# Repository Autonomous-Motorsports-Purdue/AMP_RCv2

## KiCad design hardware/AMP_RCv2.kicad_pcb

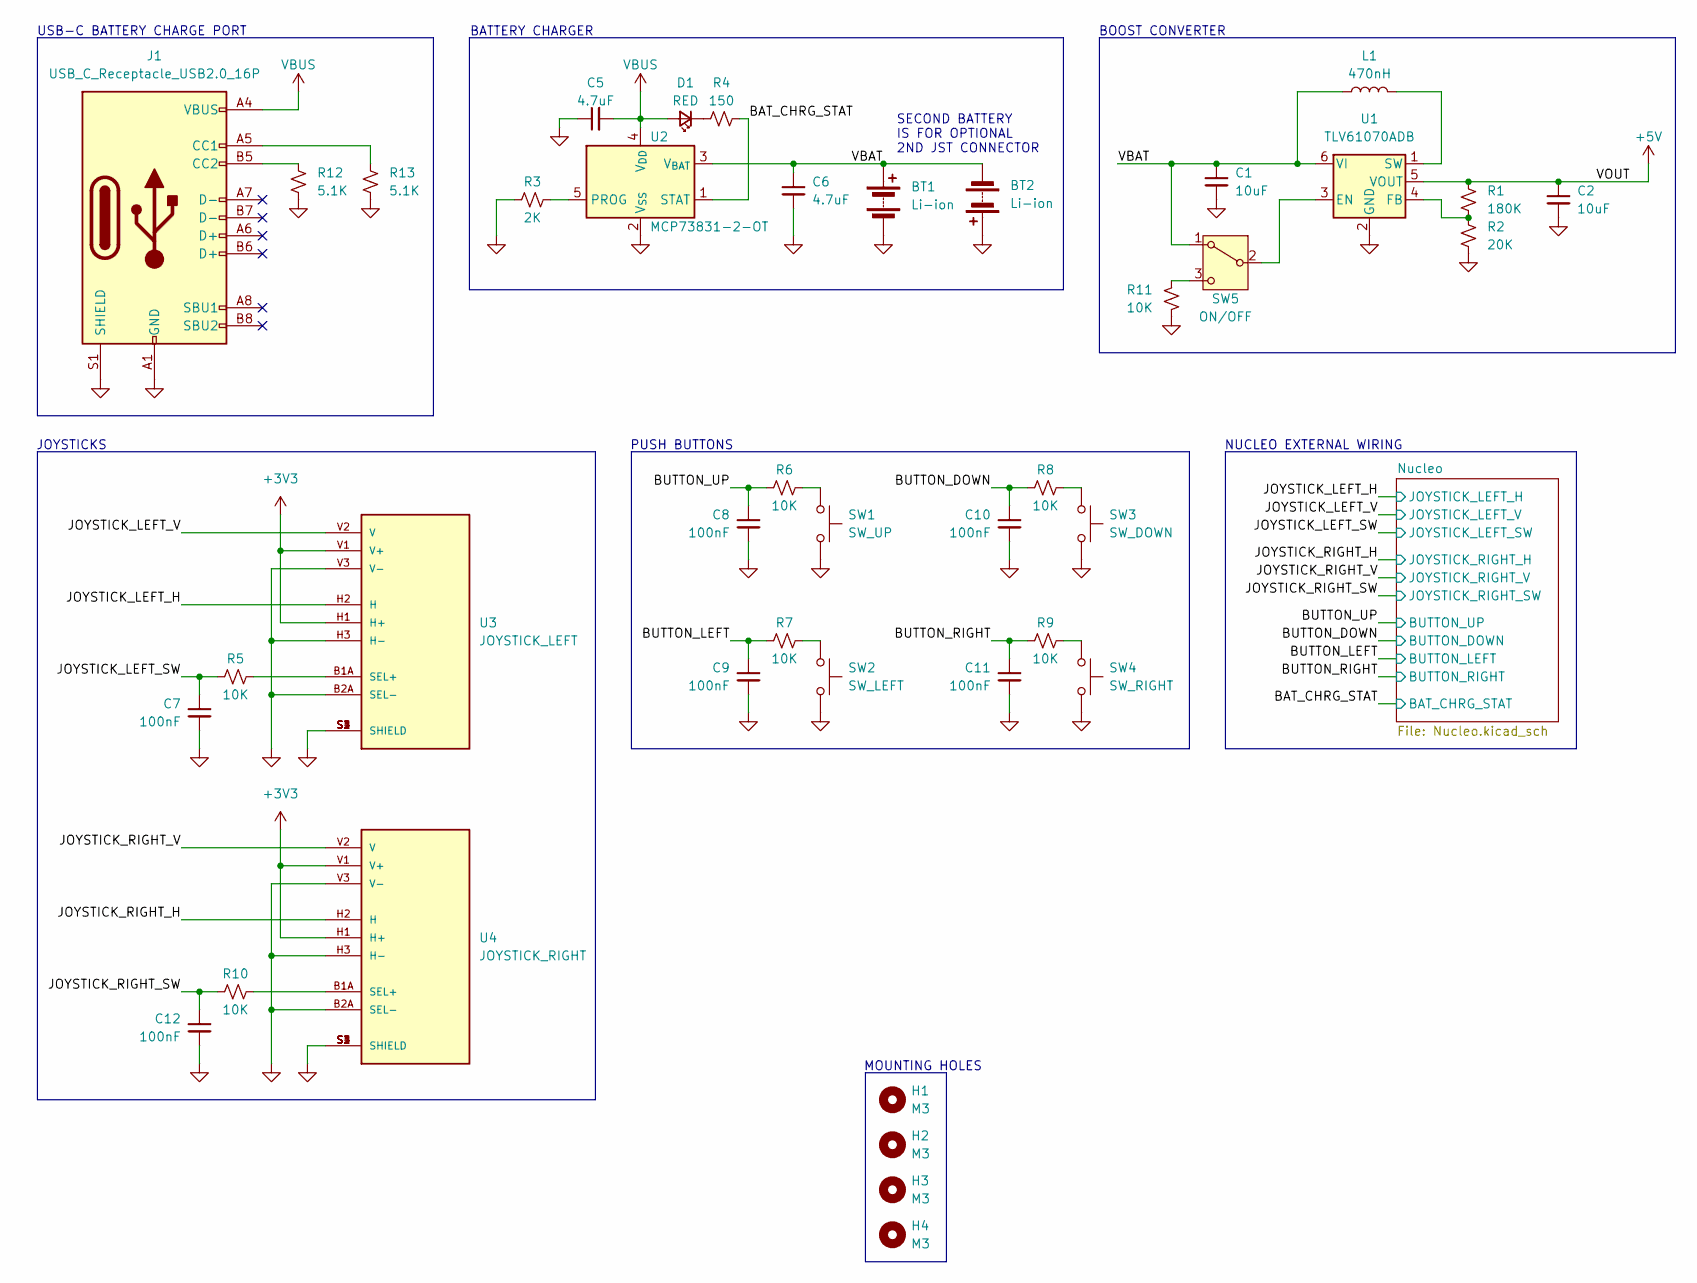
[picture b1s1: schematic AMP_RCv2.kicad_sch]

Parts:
BT1, BT2: Li-ion; JST_PH_B2B-PH-K_1x02_P2.00mm_Vertical
C1, C2: 10uF; C_0805_2012Metric_Pad1.18x1.45mm_HandSolder
C5, C6: 4.7uF; C_0805_2012Metric_Pad1.18x1.45mm_HandSolder
C7, C8, C9, C10, C11, C12: 100nF; C_0805_2012Metric_Pad1.18x1.45mm_HandSolder
D1: RED; LED_0805_2012Metric_Pad1.15x1.40mm_HandSolder
H1, H2, H3, H4: M3; MountingHole_3.2mm_M3
J1: USB_C_Receptacle_USB2.0_16P; USB_C_Receptacle_GCT_USB4085
L1: 470nH; L_Wuerth_MAPI-4030
R1: 180K; R_0805_2012Metric_Pad1.20x1.40mm_HandSolder
R2: 20K; R_0805_2012Metric_Pad1.20x1.40mm_HandSolder
R3: 2K; R_0805_2012Metric_Pad1.20x1.40mm_HandSolder
R4: 150; R_0805_2012Metric_Pad1.20x1.40mm_HandSolder
R5, R6, R7, R8, R9, R10, R11: 10K; R_0805_2012Metric_Pad1.20x1.40mm_HandSolder
R12, R13: 5.1K; R_0805_2012Metric_Pad1.20x1.40mm_HandSolder
SW1: SW_UP; SW_PUSH-12mm
SW2: SW_LEFT; SW_PUSH-12mm
SW3: SW_DOWN; SW_PUSH-12mm
SW4: SW_RIGHT; SW_PUSH-12mm
SW5: ON/OFF; SLW-121586-5A-D
U1: TLV61070ADB; SOT-23-6
U2: MCP73831-2-OT; SOT-23-5
U3: JOYSTICK_LEFT; XDCR_COM-09032; PARTREV N/A
U4: JOYSTICK_RIGHT; XDCR_COM-09032; PARTREV N/A

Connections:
+3V3: U3.H1 (H+), U3.V1 (V+), U4.H1 (H+), U4.V1 (V+); also elsewhere on the board
+5V: C2.1, R1.1, U1.5 (VOUT); also elsewhere on the board
/BAT_CHRG_STAT: R4.2, U2.1 (STAT); also elsewhere on the board
/BUTTON_DOWN: C10.1, R8.1; also elsewhere on the board
/BUTTON_LEFT: C9.1, R7.1; also elsewhere on the board
/BUTTON_RIGHT: C11.1, R9.1; also elsewhere on the board
/BUTTON_UP: C8.1, R6.1; also elsewhere on the board
/JOYSTICK_LEFT_H: U3.H2 (H); also elsewhere on the board
/JOYSTICK_LEFT_SW: C7.1, R5.1; also elsewhere on the board
/JOYSTICK_LEFT_V: U3.V2 (V); also elsewhere on the board
/JOYSTICK_RIGHT_H: U4.H2 (H); also elsewhere on the board
/JOYSTICK_RIGHT_SW: C12.1, R10.1; also elsewhere on the board
/JOYSTICK_RIGHT_V: U4.V2 (V); also elsewhere on the board
/VBAT: BT1.1 (+), BT2.2 (-), C1.1, C6.1, L1.1, SW5.1 (A), U1.6 (VI), U2.3 (V_{BAT})
GND: BT1.2 (-), BT2.1 (+), C1.2, C2.2, C5.1, C6.2, C7.2, C8.2, C9.2, C10.2, C11.2, C12.2, J1.A1 (GND), J1.A12 (GND), J1.B1 (GND), J1.B12 (GND), J1.S1 (SHIELD), R2.2, R3.1, R11.2, R12.2, R13.2, SW1.2, SW2.2, SW3.2, SW4.2, U1.2 (GND), U2.2 (V_{SS}), U3.B2A (SEL-), U3.H3 (H-), U3.S1 (SHIELD), U3.S2 (SHIELD), U3.S3 (SHIELD), U3.S4 (SHIELD), U3.V3 (V-), U4.B2A (SEL-), U4.H3 (H-), U4.S1 (SHIELD), U4.S2 (SHIELD), U4.S3 (SHIELD), U4.S4 (SHIELD), U4.V3 (V-); also elsewhere on the board
unnamed: D1.1 (K), R4.1
unnamed: J1.A5 (CC1), R13.1
unnamed: J1.B5 (CC2), R12.1
unnamed: R6.2, SW1.1
unnamed: R7.2, SW2.1
unnamed: R8.2, SW3.1
unnamed: R9.2, SW4.1
unnamed: SW5.2 (B), U1.3 (EN)
unnamed: R11.1, SW5.3 (C)
unnamed: R1.2, R2.1, U1.4 (FB)
unnamed: L1.2, U1.1 (SW)
unnamed: R3.2, U2.5 (PROG)
unnamed: R5.2, U3.B1A (SEL+)
unnamed: R10.2, U4.B1A (SEL+)
VBUS: C5.2, D1.2 (A), J1.A4 (VBUS), J1.A9 (VBUS), J1.B4 (VBUS), J1.B9 (VBUS), U2.4 (V_{DD})

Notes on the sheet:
JOYSTICKS
BATTERY CHARGER
MOUNTING HOLES
BOOST CONVERTER
USB-C BATTERY CHARGE PORT
NUCLEO EXTERNAL WIRING
PUSH BUTTONS
SECOND BATTERY IS FOR OPTIONAL 2ND JST CONNECTOR

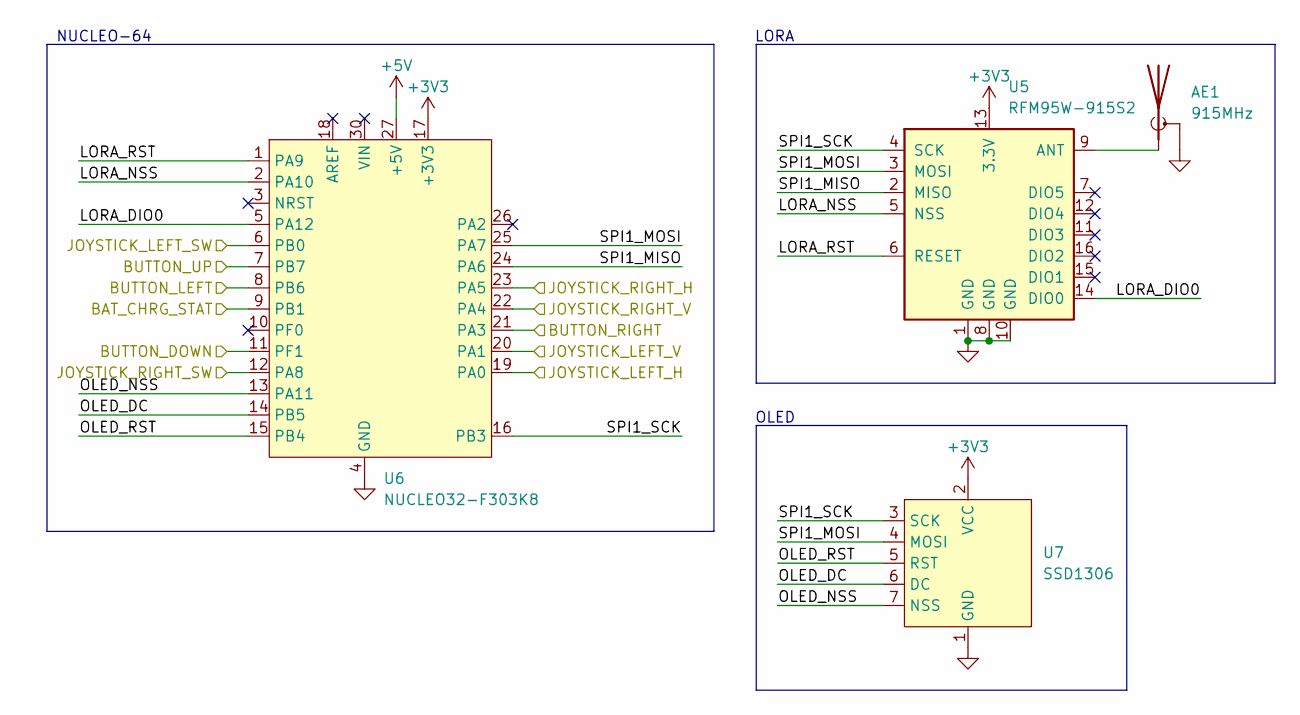
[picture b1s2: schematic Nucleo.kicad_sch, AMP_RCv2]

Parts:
AE1: 915MHz; SMA_Amphenol_132291_Vertical
U5: RFM95W-915S2; HOPERF_RFM9XW_SMD
U6: NUCLEO32-F303K8; NUCLEO32
U7: SSD1306; SSD1306_SPI

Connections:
+3V3: U5.13 (3.3V), U6.17 (+3V3), U7.2 (VCC); also elsewhere on the board
+5V: U6.27 (+5V); also elsewhere on the board
/BAT_CHRG_STAT: U6.9 (PB1); also elsewhere on the board
/BUTTON_DOWN: U6.11 (PF1); also elsewhere on the board
/BUTTON_LEFT: U6.8 (PB6); also elsewhere on the board
/BUTTON_RIGHT: U6.21 (PA3); also elsewhere on the board
/BUTTON_UP: U6.7 (PB7); also elsewhere on the board
/JOYSTICK_LEFT_H: U6.19 (PA0); also elsewhere on the board
/JOYSTICK_LEFT_SW: U6.6 (PB0); also elsewhere on the board
/JOYSTICK_LEFT_V: U6.20 (PA1); also elsewhere on the board
/JOYSTICK_RIGHT_H: U6.23 (PA5); also elsewhere on the board
/JOYSTICK_RIGHT_SW: U6.12 (PA8); also elsewhere on the board
/JOYSTICK_RIGHT_V: U6.22 (PA4); also elsewhere on the board
/Nucleo/LORA_DIO0: U5.14 (DIO0), U6.5 (PA12)
/Nucleo/LORA_NSS: U5.5 (NSS), U6.2 (PA10)
/Nucleo/LORA_RST: U5.6 (RESET), U6.1 (PA9)
/Nucleo/OLED_DC: U6.14 (PB5), U7.6 (DC)
/Nucleo/OLED_NSS: U6.13 (PA11), U7.7 (NSS)
/Nucleo/OLED_RST: U6.15 (PB4), U7.5 (RST)
/Nucleo/SPI1_MISO: U5.2 (MISO), U6.24 (PA6)
/Nucleo/SPI1_MOSI: U5.3 (MOSI), U6.25 (PA7), U7.4 (MOSI)
/Nucleo/SPI1_SCK: U5.4 (SCK), U6.16 (PB3), U7.3 (SCK)
GND: AE1.2 (Shield), U5.1 (GND), U5.8 (GND), U5.10 (GND), U6.4 (GND), U6.29 (GND), U7.1 (GND); also elsewhere on the board
unnamed: AE1.1 (A), U5.9 (ANT)

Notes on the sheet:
NUCLEO-64
OLED
LORA

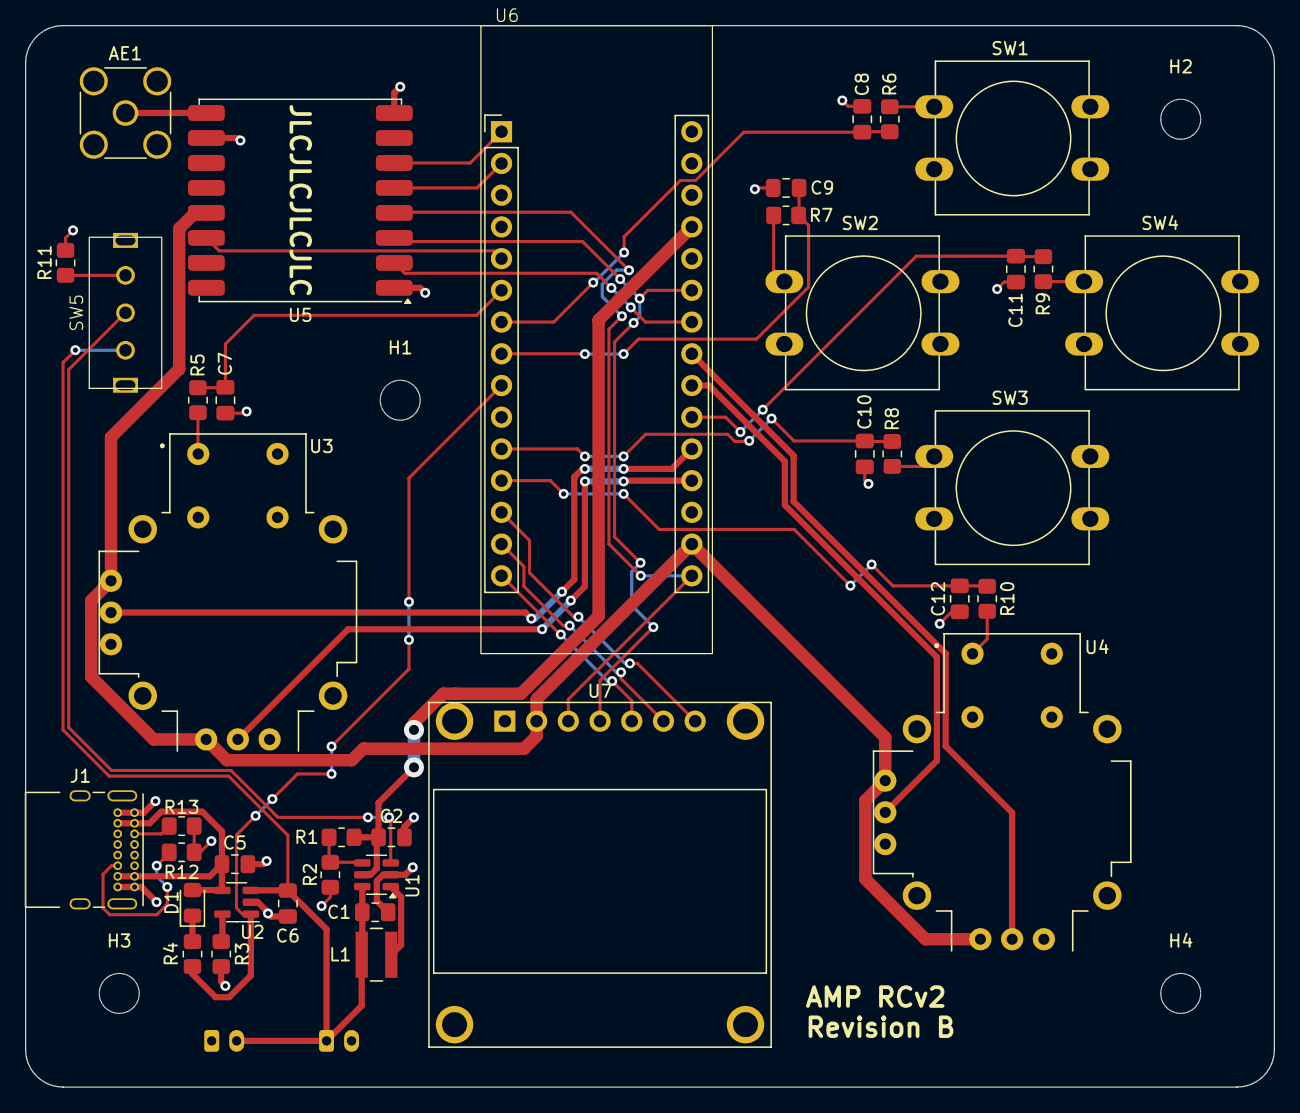
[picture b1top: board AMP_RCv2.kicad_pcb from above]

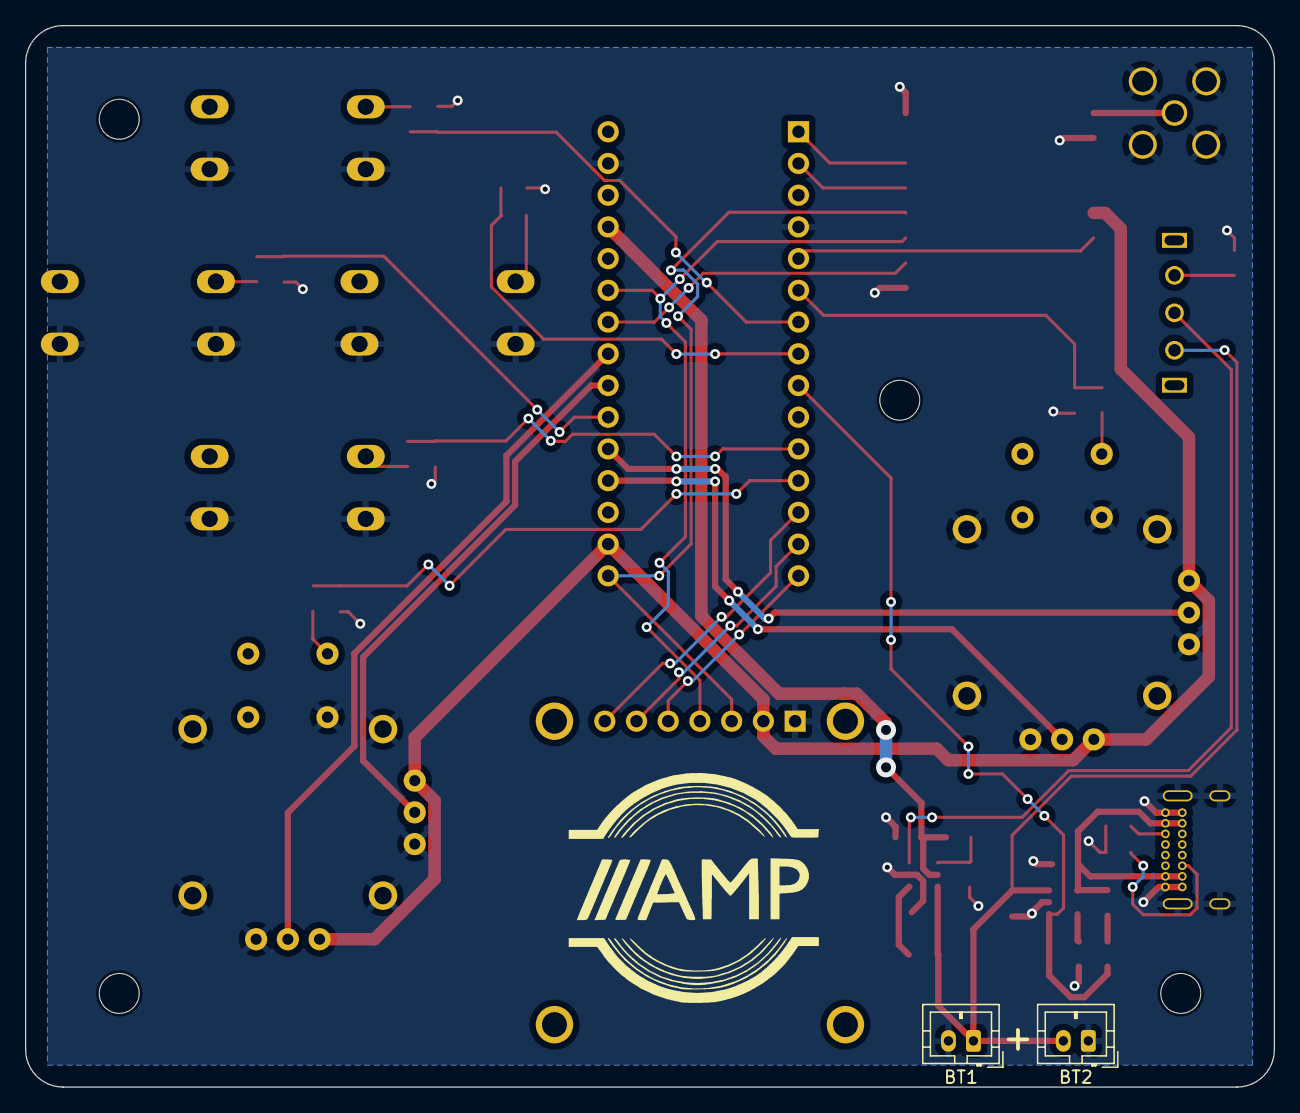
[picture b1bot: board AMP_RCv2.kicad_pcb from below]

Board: 2 copper layers, 100.0 x 85.0 mm, 45 parts (2 on the bottom side), 40 nets.

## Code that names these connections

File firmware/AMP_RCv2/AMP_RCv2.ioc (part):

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Mcu.Name=STM32F303K(6-8)Tx
Mcu.Package=LQFP32
Mcu.UserName=STM32F303K8Tx
PA0.GPIOParameters=GPIO_Label
PA0.GPIO_Label=JOYSTICK_LEFT_H
PA0.Mode=IN1-Single-Ended
PA0.Signal=ADC1_IN1
PA1.GPIOParameters=GPIO_Label
PA1.GPIO_Label=JOYSTICK_LEFT_V
PA1.Mode=IN2-Single-Ended
PA1.Signal=ADC1_IN2
PA10.GPIOParameters=GPIO_Label
PA10.GPIO_Label=LORA_NSS
PA10.Signal=GPIO_Output
PA11.GPIOParameters=GPIO_Label
PA11.GPIO_Label=OLED_NSS
PA11.Signal=GPIO_Output
PA12.GPIOParameters=GPIO_Label
PA12.GPIO_Label=LORA_DIO0
PA12.Signal=GPXTI12
PA13.GPIOParameters=GPIO_Label
PA13.GPIO_Label=SWDIO
PA13.Mode=Serial_Wire
PA13.Signal=SYS_JTMS-SWDIO
PA14.GPIOParameters=GPIO_Label
PA14.GPIO_Label=SWCLK
PA14.Mode=Serial_Wire
PA14.Signal=SYS_JTCK-SWCLK
PA15.GPIOParameters=GPIO_Label
PA15.GPIO_Label=VCP_RX
PA15.Mode=Asynchronous
PA15.Signal=USART2_RX
PA2.GPIOParameters=GPIO_Label
PA2.GPIO_Label=VCP_TX
PA2.Mode=Asynchronous
PA2.Signal=USART2_TX
PA3.GPIOParameters=GPIO_PuPd,GPIO_Label,GPIO_ModeDefaultEXTI
PA3.GPIO_Label=BTN_RIGHT
PA3.GPIO_ModeDefaultEXTI=GPIO_MODE_IT_FALLING
PA3.GPIO_PuPd=GPIO_PULLUP
PA3.Signal=GPXTI3
PA4.GPIOParameters=GPIO_Label
PA4.GPIO_Label=JOYSTICK_RIGHT_V
PA4.Mode=IN1-Single-Ended
PA4.Signal=ADC2_IN1
PA5.GPIOParameters=GPIO_Label
PA5.GPIO_Label=JOYSTICK_RIGHT_H
PA5.Mode=IN2-Single-Ended
PA5.Signal=ADC2_IN2
PA6.Mode=Full_Duplex_Master
PA6.Signal=SPI1_MISO
PA7.Mode=Full_Duplex_Master
PA7.Signal=SPI1_MOSI
PA8.GPIOParameters=GPIO_Label
PA8.GPIO_Label=JOYSTICK_R_SW
PA8.Signal=GPXTI8
PA9.GPIOParameters=GPIO_Label
PA9.GPIO_Label=LORA_RST
PA9.Signal=GPIO_Output
PB0.GPIOParameters=GPIO_Label,GPIO_ModeDefaultEXTI
PB0.GPIO_Label=JOYSTICK_L_SW
PB0.GPIO_ModeDefaultEXTI=GPIO_MODE_IT_RISING
PB0.Signal=GPXTI0
PB1.GPIOParameters=GPIO_Label
PB1.GPIO_Label=BAT_CHRG_STAT
PB1.Signal=GPIO_Input
PB3.Mode=Full_Duplex_Master
PB3.Signal=SPI1_SCK
PB4.GPIOParameters=GPIO_Label
PB4.GPIO_Label=OLED_RST
PB4.Signal=GPIO_Output
PB5.GPIOParameters=GPIO_Label
PB5.GPIO_Label=OLED_DC
PB5.Signal=GPIO_Output
PB6.GPIOParameters=GPIO_PuPd,GPIO_Label,GPIO_ModeDefaultEXTI
PB6.GPIO_Label=BTN_LEFT
PB6.GPIO_ModeDefaultEXTI=GPIO_MODE_IT_FALLING
PB6.GPIO_PuPd=GPIO_PULLUP
PB6.Signal=GPXTI6
PB7.GPIOParameters=GPIO_PuPd,GPIO_Label,GPIO_ModeDefaultEXTI
PB7.GPIO_Label=BTN_UP
PB7.GPIO_ModeDefaultEXTI=GPIO_MODE_IT_FALLING
PB7.GPIO_PuPd=GPIO_PULLUP
PB7.Signal=GPXTI7
PF0\ /\ OSC_IN.GPIOParameters=GPIO_Label
PF0\ /\ OSC_IN.GPIO_Label=MCO
PF0\ /\ OSC_IN.Mode=HSE-External-Clock-Source
PF0\ /\ OSC_IN.Signal=RCC_OSC_IN
PF1\ /\ OSC_OUT.GPIOParameters=GPIO_PuPd,GPIO_Label,GPIO_ModeDefaultEXTI
PF1\ /\ OSC_OUT.GPIO_Label=BTN_DOWN
PF1\ /\ OSC_OUT.GPIO_ModeDefaultEXTI=GPIO_MODE_IT_FALLING
PF1\ /\ OSC_OUT.GPIO_PuPd=GPIO_PULLUP
PF1\ /\ OSC_OUT.Signal=GPXTI1
RCC.HSEPLLFreq_Value=8000000
RCC.HSE_VALUE=8000000
RCC.SYSCLKFreq_VALUE=64000000
RCC.SYSCLKSourceVirtual=RCC_SYSCLKSOURCE_PLLCLK
board=NUCLEO-F303K8
boardIOC=true

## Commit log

2024-03-14 WebBench
2024-03-14 IOC mappings
2024-03-14 Schematic and placing of most parts
2024-03-15 Change IOC for better routing
2024-03-15 IOC remapping for better routing
2024-03-15 Finish routing
2024-03-15 Add Nucleo-32 docs
2024-03-15 KiCAD 8.0 migration
2024-03-27 Ignore KiCAD lck files
2024-03-27 Fix incorrect power switch wiring
2024-03-27 Replace USB-C port
2024-03-27 Increase ground plane size
2024-03-28 Replace boost converter
2024-03-28 Clean up schematic and add optional second battery connector
2024-03-28 Remove old WEBENCH design
2024-03-28 Update 3D models
2024-04-04 Finishing touches
2024-04-04 Change text size
2024-04-30 I prey to the lord this uploads
2024-05-02 Remove extra Eclipse files
2024-05-02 Ignore CubeIDE files
2024-05-02 Remove files
2024-05-02 Update gitignore
2024-05-02 Update ioc peripheral generation format
2024-05-02 Clean up state machine
2024-05-02 Revert "Remove extra Eclipse files"
    This reverts commit c2f57aa422bf200500a915565af12b525244114b.
2024-05-02 Remove unused constants
2024-09-27 Started on screen - needs hw testing
2024-10-31 screen actually works now with hello world :)
2024-10-31 created basic state screens
2024-11-01 added startup image
2025-02-02 testing code from last semester. to be removed
2025-02-02 forgot to add file
2025-03-30 init lora
2025-09-28 start of conversion
2025-09-28 removed upload port from platformio.ini
2025-10-20 Add files via upload
    Updated app_statemachine code with improved OLED display
2025-10-20 Add files via upload
    Updates supporting files for the OLED display
2025-10-26 Configured throttle and steering
2025-10-27 Implemented joystick deadzone
2026-04-26 track day
